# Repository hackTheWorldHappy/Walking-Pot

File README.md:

# WaPo Walking-Pot

A Pot on 6 Legs that walks towards the sun, to achive the best for it's flower.

While doing the project, I learned a lot of new Stuff. Before beginning this Project, I never touched a PCB modeling software. I did 3d Modelling a few time, but the best i got was a dice. So this Project is a step up. The Things I learned while doing this project, will help me a lot with other Projects.

## Key Facts
WaPo has 6 Legs with 3 Servo motors each to navigate the world.
To know where to go WaPo uses 8 light sensors/resistors to check the light levels around him.
WaPo will find the sensor with the most light, then it will rotate/move in the direction where the most light is registered. 

The PCB has a ESP Wroom chip and 2 PCA9685 LED/Servo Drivers, to be able to controll all 18 Servos at once.
The PCB fits into the bottom of the Pot.

## Why WaPo?
Besides that my plants are not living the best life (weak lightning), I want to explore Hexapods and the combination of all these servos to acctually move the robot.
Maybe that's the only way my plants can survive :)
My Idea was, to set WaPo on the Ground power it on and see where it goes to find the best Spot.

## How to Build your Own WaPo?
You can build your own WaPo by following these instructions: [INSTRUCTIONS.md](https://github.com/hackTheWorldHappy/Walking-Pot/blob/main/INSTRUCTIONS.md)

## Visuals
**Assembled 3D model**

<br>

**PCB 3D Model**

<br>

**PCB Schematic**

[WaPo-Schematic.pdf](https://github.com/hackTheWorldHappy/Walking-Pot/blob/main/SCH_WaPo-Schematic_2026-05-25.pdf)
<br>

**PCB Layout**

[PCB_wapo.pdf](https://github.com/hackTheWorldHappy/Walking-Pot/blob/main/PCB_PCB_wapo.pdf)

<br>

## Zine

As a PDF: [Zine.pdf](https://github.com/hackTheWorldHappy/Walking-Pot/blob/main/zine.pdf)

---

## BOM
Name | Quantity | Price (for all) | Price in USD |Link
:------:|:-------:|:-------:|:-------:|:-------:
PCB (x5) | 1 (5) | ~22,73€ | ~26.44$ | [JLCPCB](https://jlcpcb.com) 
Servos sg90 | 18 | ~0,70€ | ~0.81$ | [AliExpress](https://de.aliexpress.com/item/1005007104370383.html)
Light Resistors | 8 | ~24,06€ | ~27.99$ | [AliExpress](https://de.aliexpress.com/item/32966282692.html)
M2 8mm Screws | 24 | ~0,79€ | ~0.92$ | [AliExpress](https://de.aliexpress.com/item/1005002247282771.html)
M2 10mm Screws | 12 | ~0,41€ | ~0.48$ | [AliExpress](https://de.aliexpress.com/item/1005002247282771.html)
M2 Nuts | 36 | ~1,13€ | ~1.31$ | [AliExpress](https://de.aliexpress.com/item/1005008314195033.html)  
Cables | 16 | ~2,11€ | ~2.45$ | [AliExpress](https://de.aliexpress.com/item/1005007046465880.html)
4.8V 3000mAh Battery | 1 | ~9,64€ | ~11.22$ | [AliExpress](https://de.aliexpress.com/item/1005006690430909.html)
PLA Filament Spool | 1 | ~15,43€ | ~17.95$ | [Amazon](https://www.amazon.com/dp/B0CD161SQR)
Total | | ~77,67€ | ~90.37$ | [BOM-all.csv](https://github.com/hackTheWorldHappy/Walking-Pot/blob/main/BOM-all.csv)
Actual Total* | | ~102,56€ | ~119.33$

*Actual Total: Cost including shipping and actual package size (Screws/Nuts come in 50PCS, Light resistors in 10)

View the PCB BOM as CSV: [BOM-PCB.csv](https://github.com/hackTheWorldHappy/Walking-Pot/blob/main/BOM-PCB.csv) <br>
View the BOM as CSV: [BOM.csv](https://github.com/hackTheWorldHappy/Walking-Pot/blob/main/BOM.csv)

---

## Firmware
### Libaries used in Firmware
https://github.com/adafruit/Adafruit-PWM-Servo-Driver-Library/tree/master

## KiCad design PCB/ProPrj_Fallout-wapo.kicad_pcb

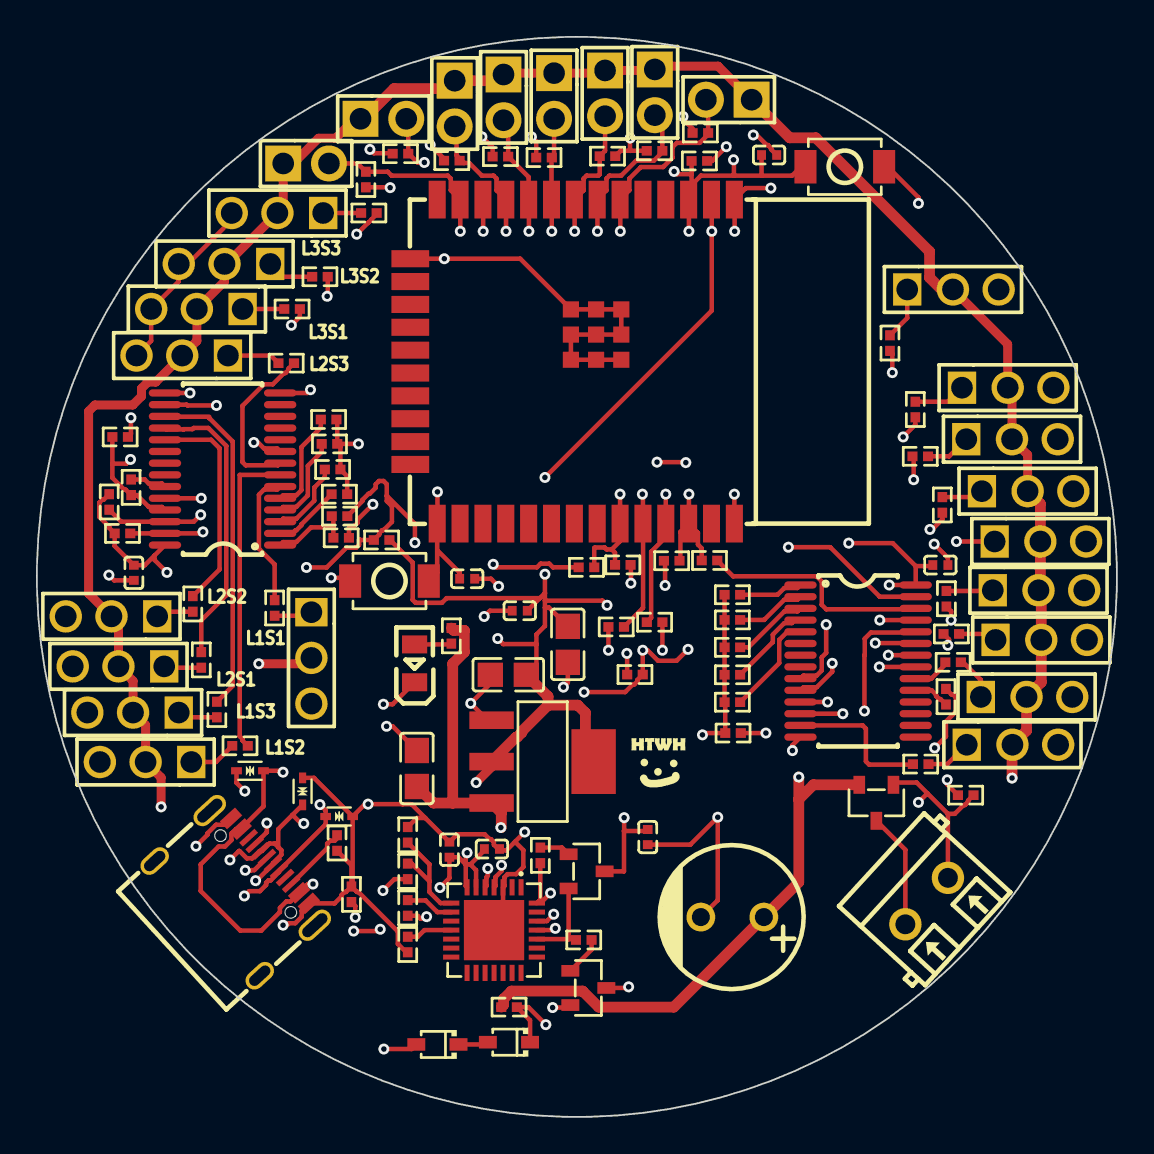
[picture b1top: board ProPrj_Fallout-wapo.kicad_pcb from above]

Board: 4 copper layers, 60.0 x 60.0 mm, 118 parts (0 on the bottom side), 90 nets.

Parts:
C1, C3, C4: C0805
C2, C5, C6, C7, C8, C9, C10, C11: C0402
C12: CAP-TH_BD8.0-P3.50-D0.6-FD
D1, D2: SOD-323_L1.8-W1.3-LS2.5-RD
D3, D4, D5: SOD-523_L1.2-W0.8-LS1.6-BI
H1, H2, H3, H4, H5, H6, H7, H8: HDR-TH_2P-P2.54-V-M
H9, H10, H11, H12, H13, H14, H15, H16, H17, H32, H33, H34, H35, H36, H37, H38, H39, H40: HDR-TH_3P-P2.54-V-M-1
LED1: LED0805-R-RD
Q1, Q2, Q3: SOT-23-3_L2.9-W1.3-P1.90-LS2.4-BR
R1, R2, R3, R4, R5, R6, R7, R8, R9, R10, R11, R12, R13, R14, R15, R16, R17, R18, R19, R20, R21, R22, R23, R24, R25, R26, R27, R28, R29, R30, R31, R32, R33, R34, R35, R36, R44, R54, R55, R56, R57, R58, R59, R60, R61, R62, R63, R64, R65, R66, R67, R68, R69, R70, R71, R72, R73, R74, R75, R76, R77, R78: R0402
SW1, SW2: SW-SMD_L3.9-W3.0-P4.45
U1: WIFI-SMD_ESP32-WROOM-32E
U2: SOT-223-4_L6.5-W3.5-P2.30-LS7.0-BR
U3: QFN-28_L5.0-W5.0-P0.50-TL-EP3.3
U4, U5: TSSOP-28_L9.7-W4.4-P0.65-LS6.4-TL
U6: CONN-TH_DB301V-3.5-2P-GN
USB1: USB-C-SMD_TYPE-C16PIN

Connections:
2_A0: R56.1, R65.2, U5.1
2_A1: R58.2, U5.2
2_A2: R59.2, U5.3
2_A3: R60.2, U5.4
2_A4: R61.2, U5.5
2_A5: R76.2, U5.24
2_OE: R44.2, U5.23
2_PWM0: R73.1, U5.6
2_PWM1: R71.1, U5.7
2_PWM2: R69.1, U5.8
2_PWM3: R62.1, U5.9
2_PWM8: R74.1, U5.15
2_PWM9: R72.1, U5.16
2_PWM10: R70.1, U5.17
2_PWM11: R63.1, U5.18
2_PWM12: R54.1, U5.19
2_SCL: R57.2, R67.1, U5.26
2_SDA: R66.2, R68.1, U5.27
5V: C12.1, H1.1, H2.1, H3.1, H4.1, H5.1, H6.1, H7.1, H8.1, H9.2, H10.2, H11.2, H12.2, H13.2, H14.2, H15.2, H16.2, H17.2, H32.2, H33.2, H34.2, H35.2, H36.2, H37.2, H38.2, H39.2, H40.2, Q3.2, R11.1
$1N6269: R23.2, R26.2, U3.8
$1N6573: R27.2, U3.9
$1N6578: R21.2, U3.11
$1N6667: Q1.1, R22.2
$1N6671: Q2.1, R30.2
$1N6829: LED1.1, R1.1
$1N7006: R12.1, USB1.B5
$1N7052: R13.1, USB1.A5
$1N8815: Q3.3, U6.1
$1N9207: H9.1, R15.2
$1N9376: H11.1, R19.2
$1N9498: H13.1, R24.2
$1N9620: H15.1, R28.2
$1N9742: H10.1, R16.2
$1N9864: H12.1, R20.2
$1N9986: H14.1, R25.2
$1N10108: H16.1, R29.2
$1N11068: H17.1, R36.2
$1N16727: H40.1, R74.2
$1N16737: H38.1, R72.2
$1N16739: H36.1, R70.2
$1N16752: H34.1, R63.2
$1N16762: H39.1, R73.2
$1N16775: H37.1, R71.2
$1N16785: H35.1, R69.2
$1N16789: H33.1, R62.2
$1N16810: H32.1, R54.2
$1N22039: D1.2, D2.1
A0: R31.2, U4.1
A1: R32.2, U4.2
A2: R33.2, U4.3
A3: R34.2, U4.4
A4: R35.2, U4.5
A5: R75.2, U4.24
DE: R18.2, U4.23
DTR: Q2.2, R22.1, U3.28
EN: C5.2, C7.2, Q1.3, R6.1, SW2.2, U1.3
EXT_5V: C4.2, D1.1, R1.2, R11.2, U2.3
GND: C1.1, C2.1, C3.1, C4.1, C5.1, C6.1, C7.1, C8.1, C9.1, C10.1, C11.1, C12.2, D3.1, D4.1, D5.1, H9.3, H10.3, H11.3, H12.3, H13.3, H14.3, H15.3, H16.3, H17.3, H32.3, H33.3, H34.3, H35.3, H36.3, H37.3, H38.3, H39.3, H40.3, LED1.2, Q3.1, R2.2, R3.2, R4.2, R5.2, R7.2, R8.2, R9.2, R10.2, R12.2, R13.2, R18.1, R21.1, R26.1, R31.1, R32.1, R33.1, R34.1, R35.1, R44.1, R58.1, R59.1, R60.1, R61.1, R65.1, R75.1, R76.1, SW1.1, SW2.1, U1.1, U1.15, U1.38, U1.39, U2.1, U3.3, U3.29, U4.14, U4.25, U5.14, U5.25, U6.2, USB1.A1B12, USB1.B1A12
IO0: C6.2, Q2.3, SW1.2, U1.25
IO14: H8.2, R10.1, U1.13
IO21: R64.1, R66.1, U1.33
IO22: R55.1, R57.1, U1.36
IO25: H2.2, R3.1, U1.10
IO26: H4.2, R5.1, U1.11
IO27: H6.2, R8.1, U1.12
IO32: H5.2, R7.1, U1.8
IO33: H7.2, R9.1, U1.9
IO34: H1.2, R2.1, U1.6
IO35: H3.2, R4.1, U1.7
PWM3: R36.1, U4.9
PWM4: R28.1, U4.10
PWM5: R24.1, U4.11
PWM6: R19.1, U4.12
PWM7: R15.1, U4.13
PWM12: R29.1, U4.19
PWM13: R25.1, U4.20
PWM14: R20.1, U4.21
PWM15: R16.1, U4.22
RTS: Q1.2, R30.1, U3.24
RXD: R14.2, U3.25
RXD0: R17.1, U1.34
SCL: R55.2, U4.26
SDA: R64.2, U4.27
TXD: R17.2, U3.26
TXD0: R14.1, U1.35
USB_DN: D4.2, U3.5, USB1.A7, USB1.B7
USB_DP: D5.2, U3.4, USB1.A6, USB1.B6
VBUS: D2.2, D3.2, R23.1, USB1.A4B9, USB1.B4A9
VCC: C10.2, C11.2, R56.2, R67.2, R68.2, R77.1, R78.1, U4.28, U5.28
VDD33: C1.2, C2.2, C3.2, C8.2, C9.2, R6.2, R27.1, R77.2, R78.2, U1.2, U2.2, U2.4, U3.6, U3.7

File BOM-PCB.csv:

No.;Quantity;Name;Comment;Designator;Footprint;Value;Manufacturer Part;Manufacturer;Supplier Part;Supplier;Price;Price * Quantity;Link
1;3;Capacitor;22uF;C1,C3,C4;C0805;22uF;CL21A226MPQNNNE;SAMSUNG(??);C29277;LCSC;0,0038 ; 0,0114  ;https://www.lcsc.com/product-detail/C29277.html
2;5;Capacitor;100nF;C2,C5,C6,C7,C9;C0402;100nF;CL05B104KO5NNNC;SAMSUNG(??);C1525;LCSC;0,0003 ; 0,0015  ;https://www.lcsc.com/product-detail/C1525.html
3;1;Capacitor;10uF;C8;C0402;10uF;CL05A106MP5NUNC;SAMSUNG(??);C315248;LCSC;0,0015 ; 0,0015  ;https://www.lcsc.com/product-detail/C315248.html
4;2;Capacitor;10uF;C10,C11;C0402;10uF;CL05A106MQ5NUNC;SAMSUNG(??);C15525;LCSC;0,0011 ; 0,0022  ;https://www.lcsc.com/product-detail/C15525.html
5;1;Capacitor;1000uF;C12;CAP-TH_BD8.0-P3.50-D0,6-FD;1000uF;KM1A102MF115A00CV0;HUAWEI(????);C189254;LCSC;0,0091 ; 0,0091  ;https://www.lcsc.com/product-detail/C189254.html
6;1;Diode;1N4148WS;D1;SOD-323_L1.8-W1.3-LS2.5-RD;;1N4148WS;CJ(????/??);C2128;LCSC;0,0014 ; 0,0014  ;https://www.lcsc.com/product-detail/C2128.html
7;1;Diode;BAT760-7;D2;SOD-323_L1.8-W1.3-LS2.5-RD;;BAT760-7;DIODES(??);C124187;LCSC;0,0092 ; 0,0092  ;https://www.lcsc.com/product-detail/C124187.html
8;3;TVS Diode;LESD5D5.0CT1G;D3,D4,D5;SOD-523_L1.2-W0,8-LS1.6-BI;;LESD5D5.0CT1G;UMW(?????);C5199850;LCSC;0,0022 ; 0,0066  ;https://www.lcsc.com/product-detail/C5199850.html
9;8;2-Pin Male Header;PZ254V-11-02P;H1,H2,H3,H4,H5,H6,H7,H8;HDR-TH_2P-P2.54-V-M;;PZ254V-11-02P;XFCN(??);C492401;LCSC;0,0024 ; 0,0192  ;https://www.lcsc.com/product-detail/C492401.html
10;18;3-Pin Male Header;2.54-1*3P?;H9,H10,H11,H12,H13,H14,H15,H16,H17,H32,H33,H34,H35,H36,H37,H38,H39,H40;HDR-TH_3P-P2.54-V-M-1;;2.54-1*3P?;BOOMELE(????);C49257;LCSC;0,0034 ; 0,0612  ;https://www.lcsc.com/product-detail/C49257.html
11;1;LED Red;KT-0805R;LED1;LED0805-R-RD;;KT-0805R;KENTO;C2295;LCSC;0,0017 ; 0,0017  ;https://www.lcsc.com/product-detail/C2295.html
12;2;Bipolar Transistor;SS8050-G(RANGE:200-350);Q1,Q2;SOT-23-3_L2.9-W1.3-P1.90-LS2.4-BR;;SS8050-G(RANGE:200-350);CJ(????/??);C164885;LCSC;0,0023 ; 0,0046  ;https://www.lcsc.com/product-detail/C164885.html
13;1;MOSFET;IRLML6401;Q3;SOT-23-3_L2.9-W1.3-P1.90-LS2.4-BR;;IRLML6401;KEXIN(??);C382329;LCSC;0,0057 ; 0,0057  ;https://www.lcsc.com/product-detail/C382329.html
14;1;Resistor;2k?;R1;R0402;2k?;0402WGF2001TCE;UNI-ROYAL(??);C4109;LCSC;0,0002 ; 0,0002  ;https://www.lcsc.com/product-detail/C4109.html
15;28;Resistor;10k?;R2,R3,R4,R5,R6,R7,R8,R9,R10,R18,R21,R22,R30,R31,R32,R33,R34,R35,R44,R58,R59,R60,R61,R65,R67,R68,R75,R76;R0402;10k?;FRC0402F1002TS;FOJAN(??);C2906861;LCSC;0,0001 ; 0,0028  ;https://www.lcsc.com/product-detail/C2906861.html
16;10;Resistor;0?;R11,R14,R17,R55,R56,R57,R64,R66,R77,R78;R0402;0?;RC0402FR-070RL;YAGEO(??);C106231;LCSC;0,0002 ; 0,0020  ;https://www.lcsc.com/product-detail/C106231.html
17;2;Resistor;5.1k?;R12,R13;R0402;5.1k?;0402WGF5101TCE;UNI-ROYAL(??);C25905;LCSC;0,0002 ; 0,0004  ;https://www.lcsc.com/product-detail/C25905.html
18;18;Resistor;220?;R15,R16,R19,R20,R24,R25,R28,R29,R36,R54,R62,R63,R69,R70,R71,R72,R73,R74;R0402;220?;0402WGF2200TCE;UNI-ROYAL(??);C25091;LCSC;0,0002 ; 0,0036  ;https://www.lcsc.com/product-detail/C25091.html
19;1;Resistor;22.1k?;R23;R0402;22.1k?;0402WGF2212TCE;UNI-ROYAL(??);C43473;LCSC;0,0002 ; 0,0002  ;https://www.lcsc.com/product-detail/C43473.html
20;1;Resistor;47.5k?;R26;R0402;47.5k?;0402WGF4752TCE;UNI-ROYAL(??);C25896;LCSC;0,0002 ; 0,0002  ;https://www.lcsc.com/product-detail/C25896.html
21;1;Resistor;1k?;R27;R0402;1k?;0402WGF1001TCE;UNI-ROYAL(??);C11702;LCSC;0,0002 ; 0,0002  ;https://www.lcsc.com/product-detail/C11702.html
22;2;Tactile Switch;TS-1088-AR02016;SW1,SW2;SW-SMD_L3.9-W3.0-P4.45;;TS-1088-AR02016;XUNPU(??);C720477;LCSC;0,0084 ; 0,0168  ;https://www.lcsc.com/product-detail/C720477.html
23;1;ESP32 Microcontroller;2.4GHz;U1;WIFI-SMD_ESP32-WROOM-32E;2.4GHz;ESP32-WROOM-32E-N16;ESPRESSIF(??);C701343;LCSC;0,6900 ; 0,6900  ;https://www.lcsc.com/product-detail/C701343.html
24;1;Voltage Regulator 1A;AMS1117-3.3;U2;SOT-223-4_L6.5-W3.5-P2.30-LS7.0-BR;;AMS1117-3.3;UMW(?????);C347222;LCSC;0,0063 ; 0,0063  ;https://www.lcsc.com/product-detail/C347222.html
25;1;USB-to-UART Bridge;CP2102N-A02-GQFN28R;U3;QFN-28_L5.0-W5.0-P0,50-TL-EP3.3;;CP2102N-A02-GQFN28R;SKYWORKS/SILICON LABS(??);C964632;LCSC;0,2422 ; 0,2422  ;https://www.lcsc.com/product-detail/C964632.html
26;2;PWM Controller;PCA9685PW,118;U4,U5;TSSOP-28_L9.7-W4.4-P0,65-LS6.4-TL;-;PCA9685PW,118;NXP(???);C2678753;LCSC;0,4910 ; 0,9820  ;https://www.lcsc.com/product-detail/C2678753.html
27;1;2 Wire to Board;DB301V-3.5-2P-GN-S;U6;CONN-TH_DB301V-3.5-2P-GN;;DB301V-3.5-2P-GN-S;DORABO(????);C695629;LCSC;0,0139 ; 0,0139  ;https://www.lcsc.com/product-detail/C695629.html
28;1;USB-C Connector;TYPE-C16PIN;USB1;USB-C-SMD_TYPE-C16PIN;;TYPE-C16PIN;SHOU HAN(??);C393939;LCSC;0,0106 ; 0,0106  ;https://www.lcsc.com/product-detail/C393939.html

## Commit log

2026-06-04 init
2026-06-04 Rename BOM-all.csv to BOM.csv
2026-06-04 Rename BOM.csv to BOM-with-total-note.csv
2026-06-04 Fix formatting and add separator in BOM.csv
    Updated BOM.csv to correct formatting and add separator.
